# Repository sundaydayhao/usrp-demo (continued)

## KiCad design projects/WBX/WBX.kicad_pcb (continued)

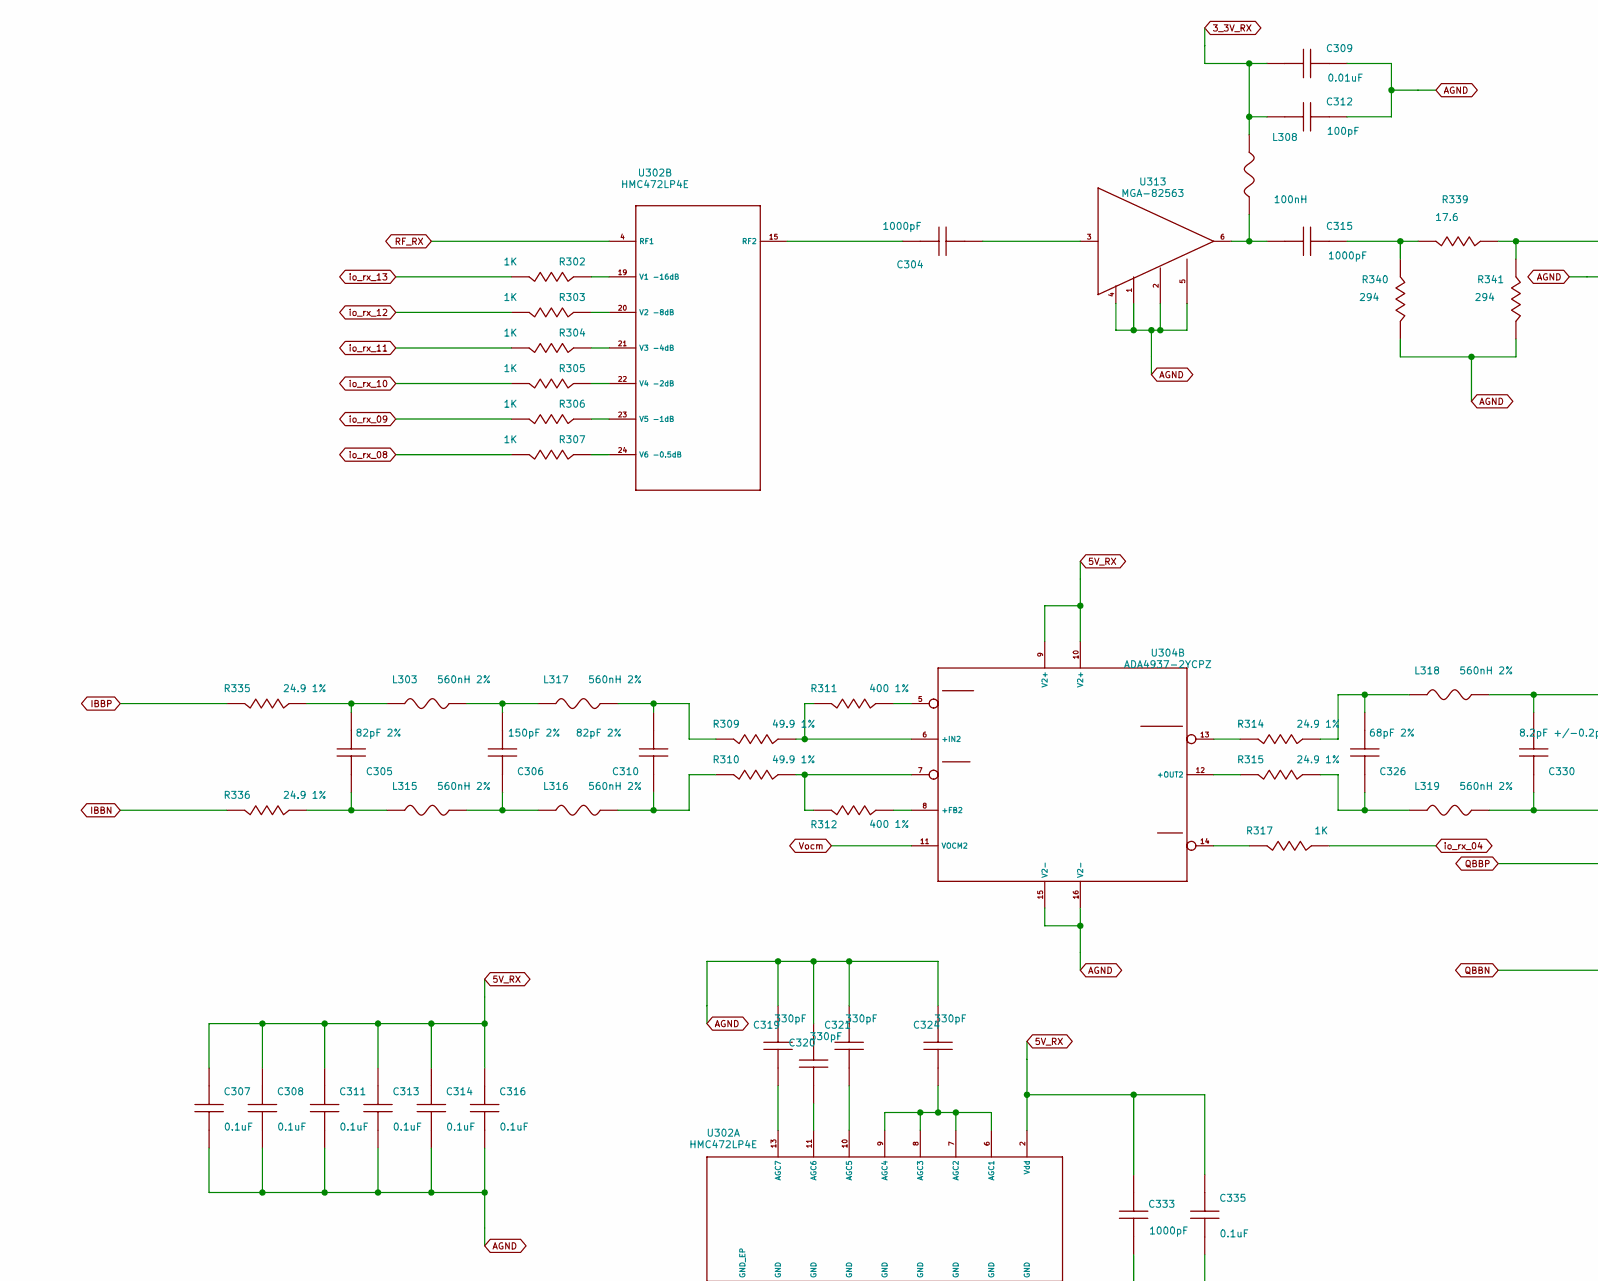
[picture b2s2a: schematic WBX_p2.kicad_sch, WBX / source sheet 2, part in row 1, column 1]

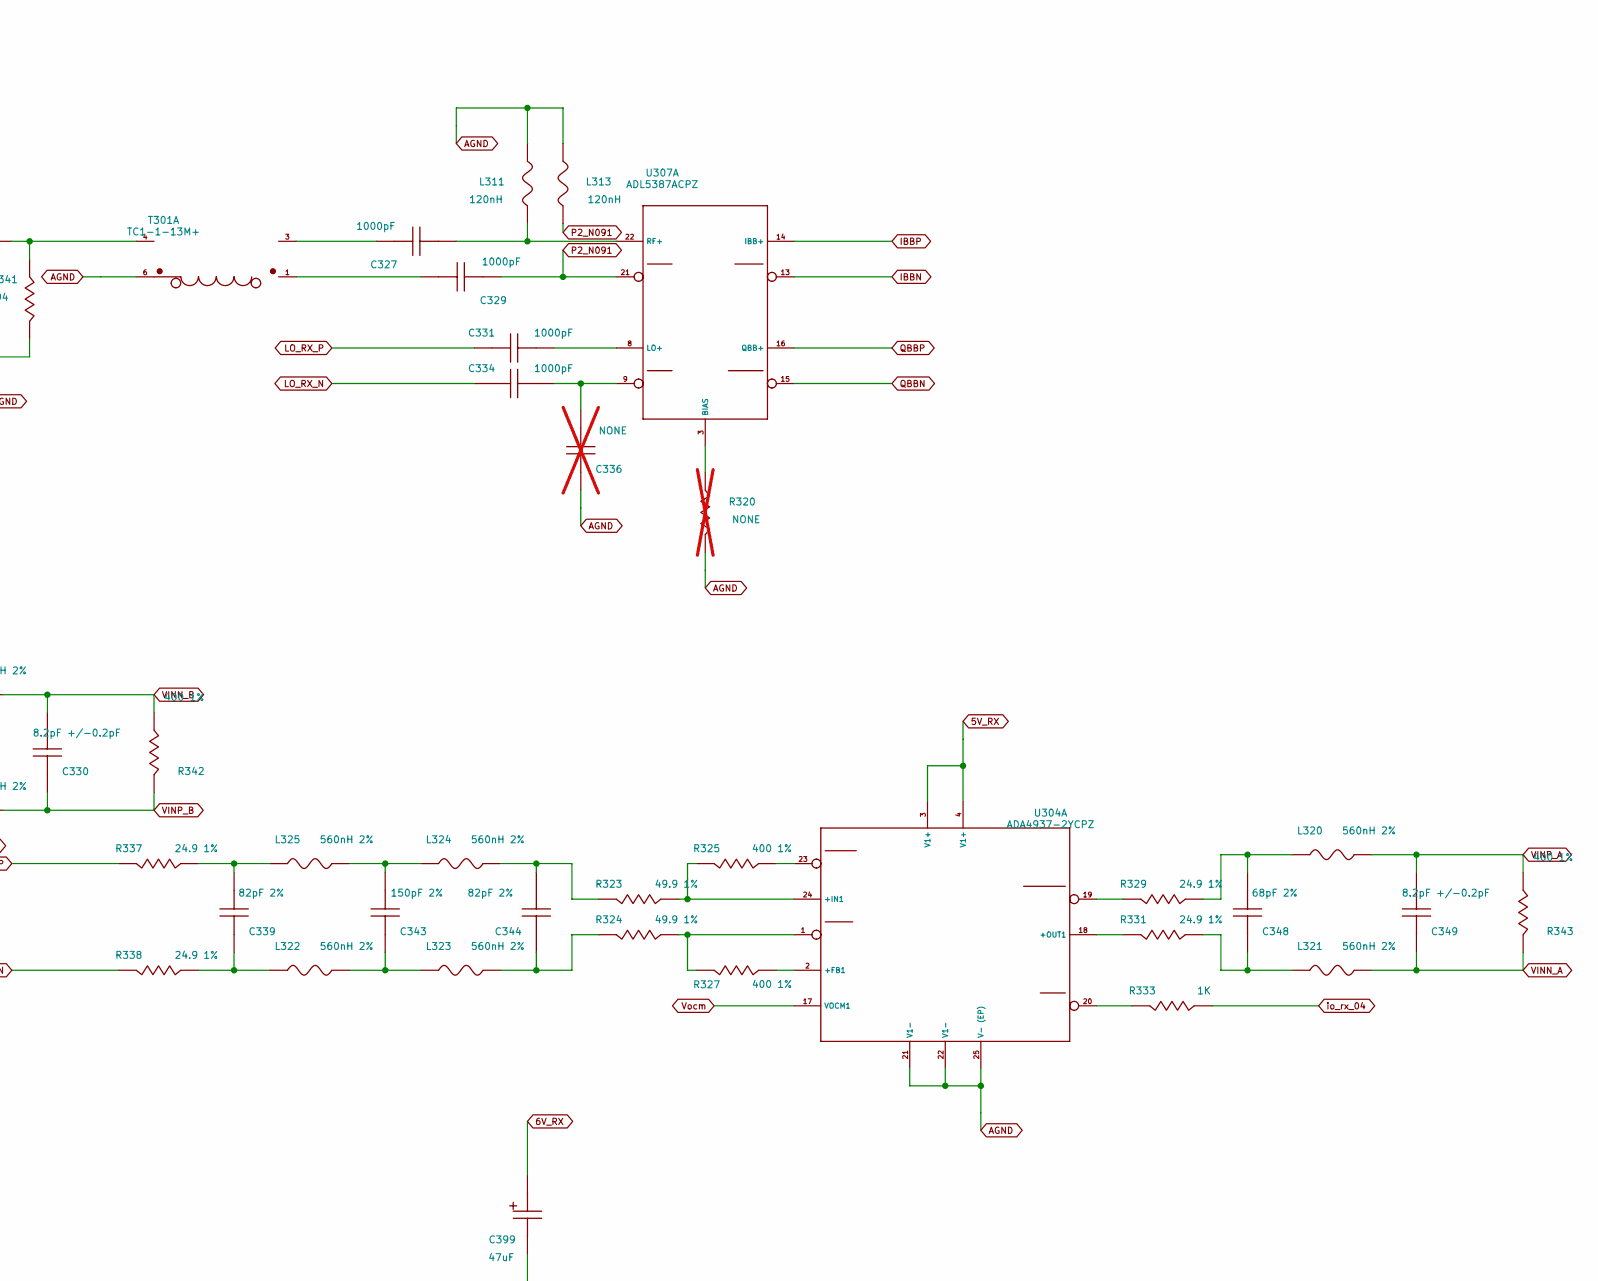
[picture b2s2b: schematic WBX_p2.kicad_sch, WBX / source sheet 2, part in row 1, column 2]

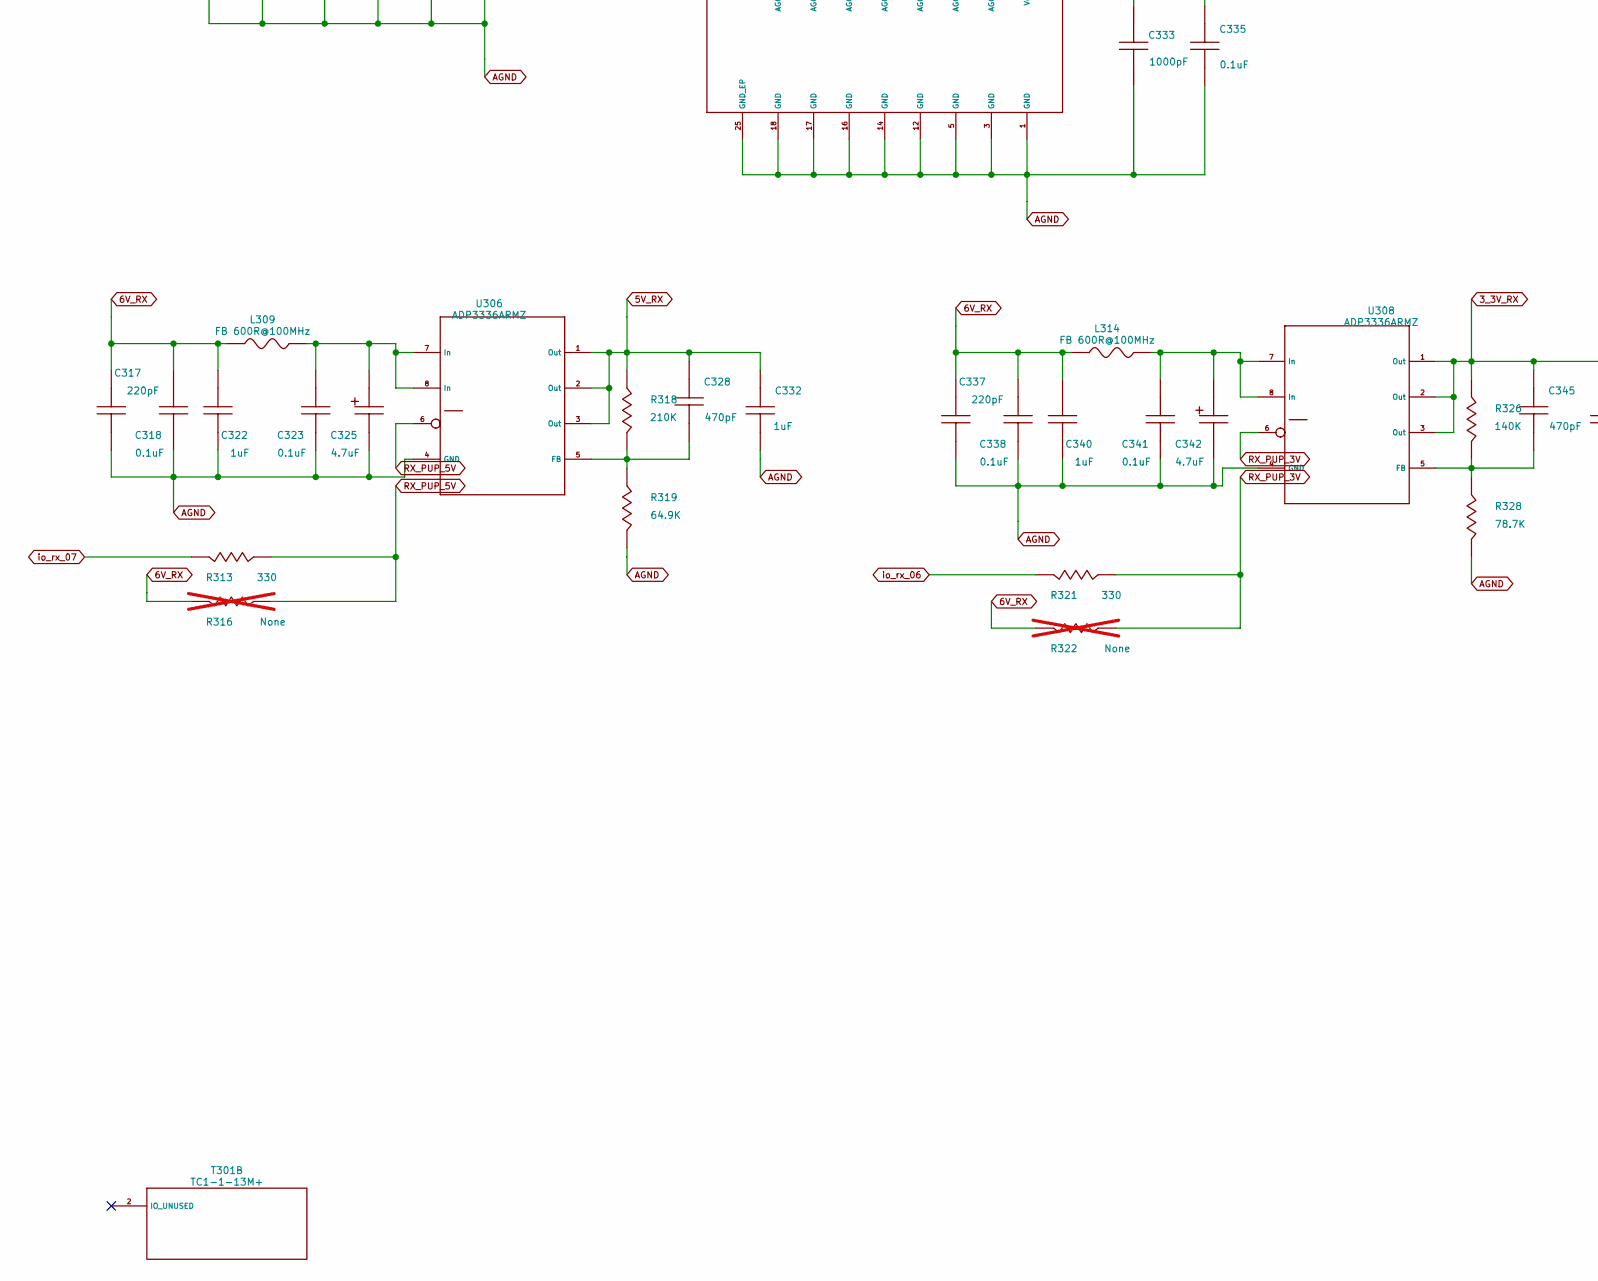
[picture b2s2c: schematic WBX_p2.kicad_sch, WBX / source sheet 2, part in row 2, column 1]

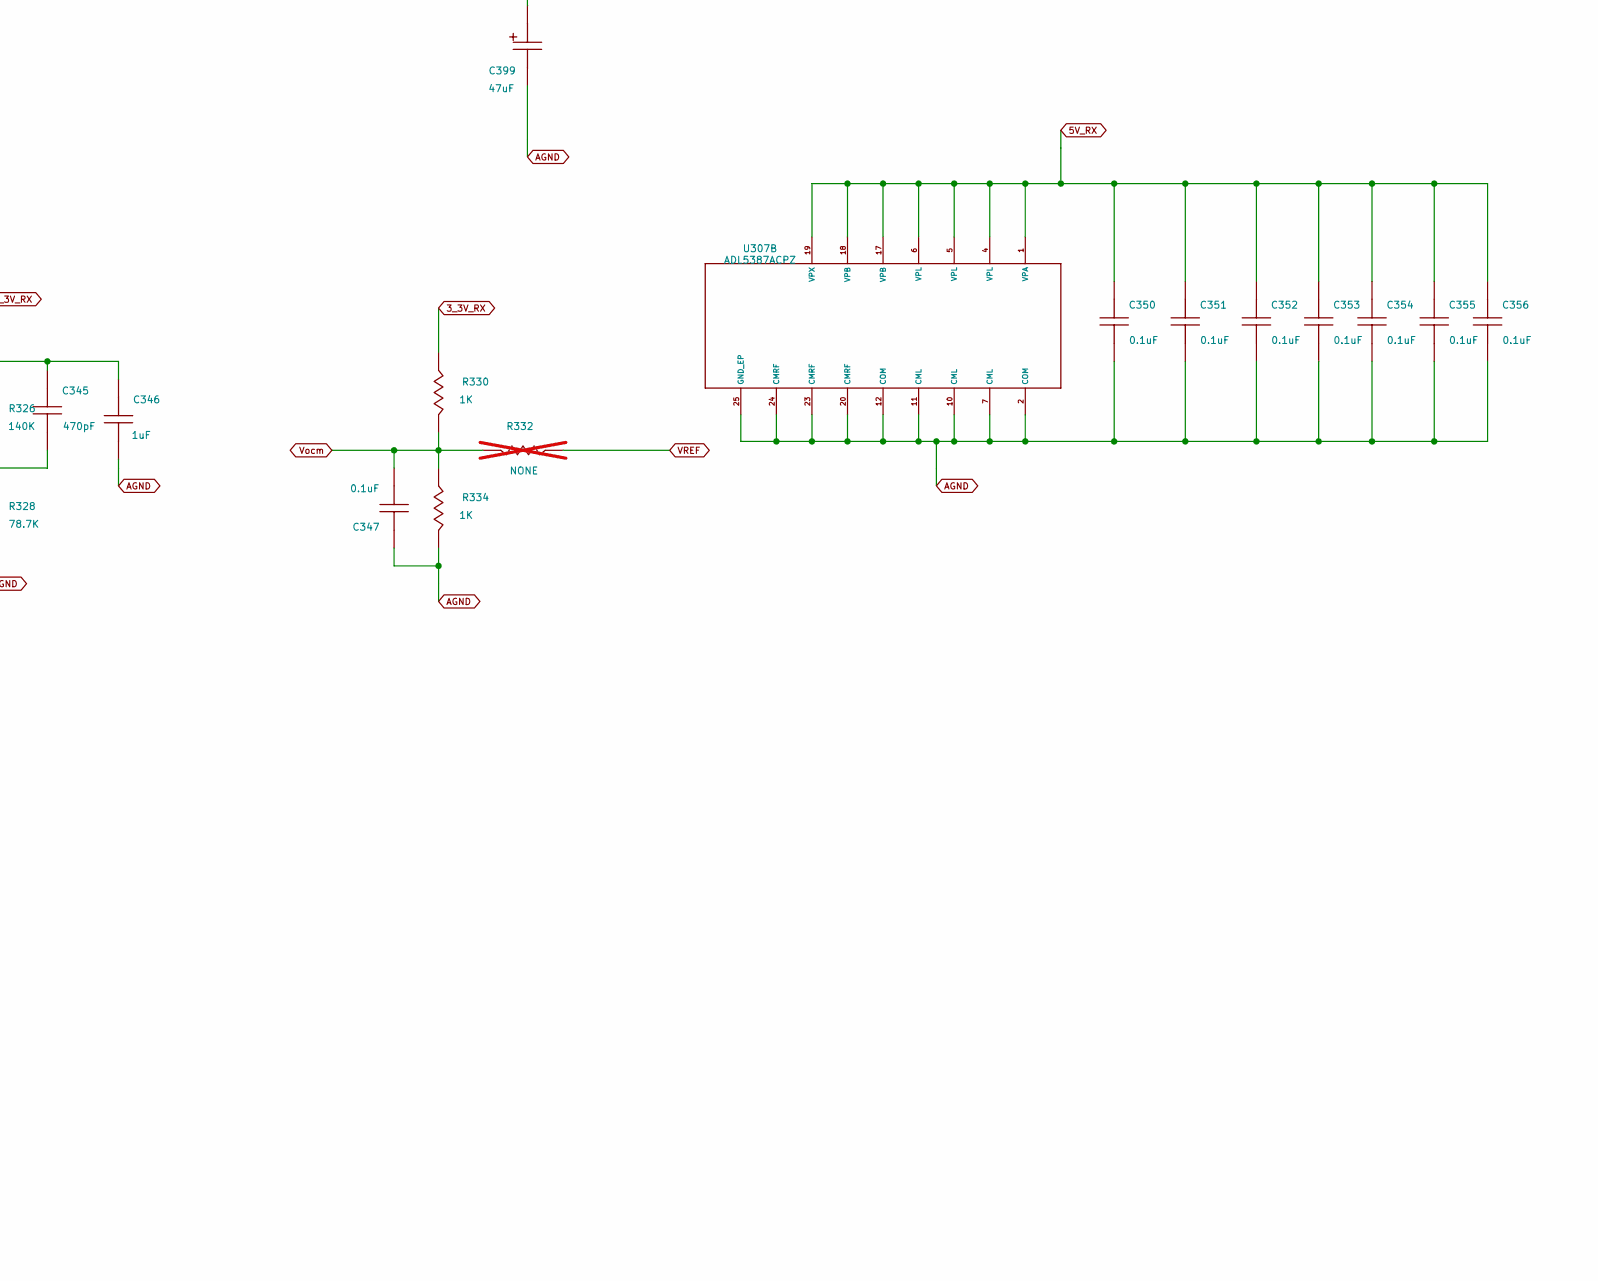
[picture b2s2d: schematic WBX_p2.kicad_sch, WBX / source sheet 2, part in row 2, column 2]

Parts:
C304: 1000pF; C304
C305: 82pF 2%; C305
C306: 150pF 2%; C306
C307: 0.1uF; C307; MPN CL05B104KO5NNNC; LCSC C1525
C308: 0.1uF; C308; MPN CL05B104KO5NNNC; LCSC C1525
C309: 0.01uF; C309
C310: 82pF 2%; C310
C311: 0.1uF; C311; MPN CL05B104KO5NNNC; LCSC C1525
C312: 100pF; C312
C313: 0.1uF; C313; MPN CL05B104KO5NNNC; LCSC C1525
C314: 0.1uF; C314; MPN CL05B104KO5NNNC; LCSC C1525
C315: 1000pF; C315
C316: 0.1uF; C316; MPN CL05B104KO5NNNC; LCSC C1525
C317: 220pF; C317
C318: 0.1uF; C318; MPN CL05B104KO5NNNC; LCSC C1525
C319: 330pF; C319
C320: 330pF; C320
C321: 330pF; C321
C322: 1uF; C322
C323: 0.1uF; C323
C324: 330pF; C324
C325: 4.7uF; C325
C326: 68pF 2%; C326
C327: 1000pF; C327
C328: 470pF; C328
C329: 1000pF; C329
C330: 8.2pF +/-0.2pF; C330
C331: 1000pF; C331
C332: 1uF; C332
C333: 1000pF; C333
C334: 1000pF; C334
C335: 0.1uF; C335; MPN CL05B104KO5NNNC; LCSC C1525
C336: NONE; C336; not fitted
C337: 220pF; C337
C338: 0.1uF; C338; MPN CL05B104KO5NNNC; LCSC C1525
C339: 82pF 2%; C339
C340: 1uF; C340
C341: 0.1uF; C341
C342: 4.7uF; C342
C343: 150pF 2%; C343
C344: 82pF 2%; C344
C345: 470pF; C345
C346: 1uF; C346
C347: 0.1uF; C347
C348: 68pF 2%; C348
C349: 8.2pF +/-0.2pF; C349
C350: 0.1uF; C350; MPN CL05B104KO5NNNC; LCSC C1525
C351: 0.1uF; C351; MPN CL05B104KO5NNNC; LCSC C1525
C352: 0.1uF; C352; MPN CL05B104KO5NNNC; LCSC C1525
C353: 0.1uF; C353; MPN CL05B104KO5NNNC; LCSC C1525
C354: 0.1uF; C354; MPN CL05B104KO5NNNC; LCSC C1525
C355: 0.1uF; C355; MPN CL05B104KO5NNNC; LCSC C1525
C356: 0.1uF; C356; MPN CL05B104KO5NNNC; LCSC C1525
C399: 47uF; C399
L303: 560nH 2%; L303
L308: 100nH; L308
L309: FB 600R@100MHz; L309
L311: 120nH; L311
L313: 120nH; L313
L314: FB 600R@100MHz; L314
L315: 560nH 2%; L315
L316: 560nH 2%; L316
L317: 560nH 2%; L317
L318: 560nH 2%; L318
L319: 560nH 2%; L319
L320: 560nH 2%; L320
L321: 560nH 2%; L321
L322: 560nH 2%; L322
L323: 560nH 2%; L323
L324: 560nH 2%; L324
L325: 560nH 2%; L325
R302: 1K; R302; MPN RC0402FR-071KL; LCSC C106235
R303: 1K; R303; MPN RC0402FR-071KL; LCSC C106235
R304: 1K; R304; MPN RC0402FR-071KL; LCSC C106235
R305: 1K; R305; MPN RC0402FR-071KL; LCSC C106235
R306: 1K; R306; MPN RC0402FR-071KL; LCSC C106235
R307: 1K; R307; MPN RC0402FR-071KL; LCSC C106235
R309: 49.9 1%; R309
R310: 49.9 1%; R310
R311: 400 1%; R311
R312: 400 1%; R312
R313: 330; R313
R314: 24.9 1%; R314
R315: 24.9 1%; R315
R316: None; R316; not fitted
R317: 1K; R317; MPN RC0402FR-071KL; LCSC C106235
R318: 210K; R318
R319: 64.9K; R319
R320: NONE; R320; not fitted
R321: 330; R321
R322: None; R322; not fitted
R323: 49.9 1%; R323
R324: 49.9 1%; R324
R325: 400 1%; R325
R326: 140K; R326
R327: 400 1%; R327
R328: 78.7K; R328
R329: 24.9 1%; R329
R330: 1K; R330; MPN RC0402FR-071KL; LCSC C106235
R331: 24.9 1%; R331
R332: NONE; R332; not fitted
R333: 1K; R333; MPN RC0402FR-071KL; LCSC C106235
R334: 1K; R334; MPN RC0402FR-071KL; LCSC C106235
R335: 24.9 1%; R335
R336: 24.9 1%; R336
R337: 24.9 1%; R337
R338: 24.9 1%; R338
R339: 17.6; R339
R340: 294; R340
R341: 294; R341
R342: 400 1%; R342
R343: 400 1%; R343
T301: TC1-1-13M+; T301; MPN TC1-1-13M+
U302: HMC472LP4E; U302; MPN HMC472LP4E
U304: ADA4937-2YCPZ; U304; MPN ADA4937-2YCPZ
U306: ADP3336ARMZ; U306; MPN ADP3336ARMZ
U307: ADL5387ACPZ; U307; MPN ADL5387ACPZ
U308: ADP3336ARMZ; U308; MPN ADP3336ARMZ
U313: MGA-82563; U313; MPN MGA-82563

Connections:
3_3V_RX: C309.2, C312.2, C345.1, C346.1, L308.1, R326.1, R330.1, U308.1 (Out), U308.2 (Out), U308.3 (Out); also elsewhere on the board
5V_RX: C307.1, C308.1, C311.1, C313.1, C314.1, C316.1, C328.1, C332.1, C333.1, C335.1, C350.1, C351.1, C352.1, C353.1, C354.1, C355.1, C356.1, R318.1, U302.2 (Vdd), U304.3 (V1+), U304.4 (V1+), U304.9 (V2+), U304.10 (V2+), U306.1 (Out), U306.2 (Out), U306.3 (Out), U307.1 (VPA), U307.4 (VPL), U307.5 (VPL), U307.6 (VPL), U307.17 (VPB), U307.18 (VPB), U307.19 (VPX); also elsewhere on the board
6V_RX: C317.1, C318.1, C322.1, C337.1, C338.1, C340.1, C399.1, L309.2, L314.2, R316.2, R322.2; also elsewhere on the board
AGND: C307.2, C308.2, C309.1, C311.2, C312.1, C313.2, C314.2, C316.2, C317.2, C318.2, C319.1, C320.1, C321.1, C322.2, C323.2, C324.1, C325.2, C332.2, C333.2, C335.2, C336.2, C337.2, C338.2, C340.2, C341.2, C342.2, C346.2, C347.2, C350.2, C351.2, C352.2, C353.2, C354.2, C355.2, C356.2, C399.2, L311.1, L313.1, R319.2, R320.2, R328.2, R334.2, R340.2, R341.2, T301.6, U302.1 (GND), U302.3 (GND), U302.5 (GND), U302.12 (GND), U302.14 (GND), U302.16 (GND), U302.17 (GND), U302.18 (GND), U302.25 (GND_EP), U304.15 (V2−), U304.16 (V2−), U304.21 (V1−), U304.22 (V1−), U304.25 (V− (EP)), U306.4 (GND), U307.2 (COM), U307.7 (CML), U307.10 (CML), U307.11 (CML), U307.12 (COM), U307.20 (CMRF), U307.23 (CMRF), U307.24 (CMRF), U307.25 (GND_EP), U308.4 (GND), U313.1, U313.2, U313.4, U313.5; also elsewhere on the board
IBBN: R336.2, U307.13
IBBP: R335.2, U307.14 (IBB+)
LO_RX_N: C334.2; also elsewhere on the board
LO_RX_P: C331.2; also elsewhere on the board
unnamed: C304.1, U313.3
unnamed: C305.1, L303.2, R335.1
unnamed: C305.2, L315.2, R336.1
unnamed: C306.1, L303.1, L317.2
unnamed: C306.2, L315.1, L316.2
unnamed: C310.1, L317.1, R309.2
unnamed: C310.2, L316.1, R310.2
unnamed: C315.1, R339.2, R340.1
unnamed: C315.2, L308.2, U313.6
unnamed: C323.1, C325.1, L309.1, U306.7 (In), U306.8 (In)
unnamed: C326.1, L318.2, R314.1
unnamed: C326.2, L319.2, R315.1
unnamed: C327.2, T301.3
unnamed: C329.2, T301.1
unnamed: C334.1, C336.1, U307.9
unnamed: C339.1, L325.2, R337.1
unnamed: C339.2, L322.2, R338.1
unnamed: C341.1, C342.1, L314.1, U308.7 (In), U308.8 (In)
unnamed: C343.1, L324.2, L325.1
unnamed: C343.2, L322.1, L323.2
unnamed: C344.1, L324.1, R323.2
unnamed: C344.2, L323.1, R324.2
unnamed: C348.1, L320.2, R329.1
unnamed: C348.2, L321.2, R331.1
unnamed: R310.1, R312.2, U304.7
unnamed: R311.1, U304.5
unnamed: R314.2, U304.13
unnamed: R317.2, U304.14
unnamed: R324.1, R327.2, U304.1
unnamed: R325.1, U304.23
unnamed: R329.2, U304.19
unnamed: R333.2, U304.20
unnamed: R339.1, R341.1, T301.4
unnamed: C324.2, U302.6 (AGC1), U302.7 (AGC2), U302.8 (AGC3), U302.9 (AGC4)
unnamed: C321.2, U302.10 (AGC5)
unnamed: C320.2, U302.11 (AGC6)
unnamed: C319.2, U302.13 (AGC7)
unnamed: C304.2, U302.15 (RF2)
unnamed: R302.1, U302.19 (V1 −16dB)
unnamed: R303.1, U302.20 (V2 −8dB)
unnamed: R304.1, U302.21 (V3 −4dB)
unnamed: R305.1, U302.22 (V4 −2dB)
unnamed: R306.1, U302.23 (V5 −1dB)
unnamed: R307.1, U302.24 (V6 −0.5dB)
unnamed: R327.1, U304.2 (+FB1)
unnamed: R323.1, R325.2, U304.24 (+IN1)
unnamed: R331.2, U304.18 (+OUT1)
unnamed: R312.1, U304.8 (+FB2)
unnamed: R309.1, R311.2, U304.6 (+IN2)
unnamed: R315.2, U304.12 (+OUT2)
unnamed: C328.2, R318.2, R319.1, U306.5 (FB)
unnamed: R320.1, U307.3 (BIAS)
unnamed: C331.1, U307.8 (LO+)
unnamed: C327.1, L311.2, U307.22 (RF+)
unnamed: C345.2, R326.2, R328.1, U308.5 (FB)
P2_N091: C329.1, L313.2, U307.21
QBBN: R338.2, U307.15
QBBP: R337.2, U307.16 (QBB+)
RF_RX: U302.4 (RF1); also elsewhere on the board
RX_PUP_3V: R321.1, R322.1, U308.6
RX_PUP_5V: R313.1, R316.1, U306.6
VINN_A: C349.2, L321.1, R343.2; also elsewhere on the board
VINN_B: C330.1, L318.1, R342.1; also elsewhere on the board
VINP_A: C349.1, L320.1, R343.1; also elsewhere on the board
VINP_B: C330.2, L319.1, R342.2; also elsewhere on the board
VREF: R332.1; also elsewhere on the board
Vocm: C347.1, R330.2, R332.2, R334.1, U304.11 (VOCM2), U304.17 (VOCM1)
io_rx_04: R317.1, R333.1; also elsewhere on the board
io_rx_06: R321.2; also elsewhere on the board
io_rx_07: R313.2; also elsewhere on the board
io_rx_08: R307.2; also elsewhere on the board
io_rx_09: R306.2; also elsewhere on the board
io_rx_10: R305.2; also elsewhere on the board
io_rx_11: R304.2; also elsewhere on the board
io_rx_12: R303.2; also elsewhere on the board
io_rx_13: R302.2; also elsewhere on the board
